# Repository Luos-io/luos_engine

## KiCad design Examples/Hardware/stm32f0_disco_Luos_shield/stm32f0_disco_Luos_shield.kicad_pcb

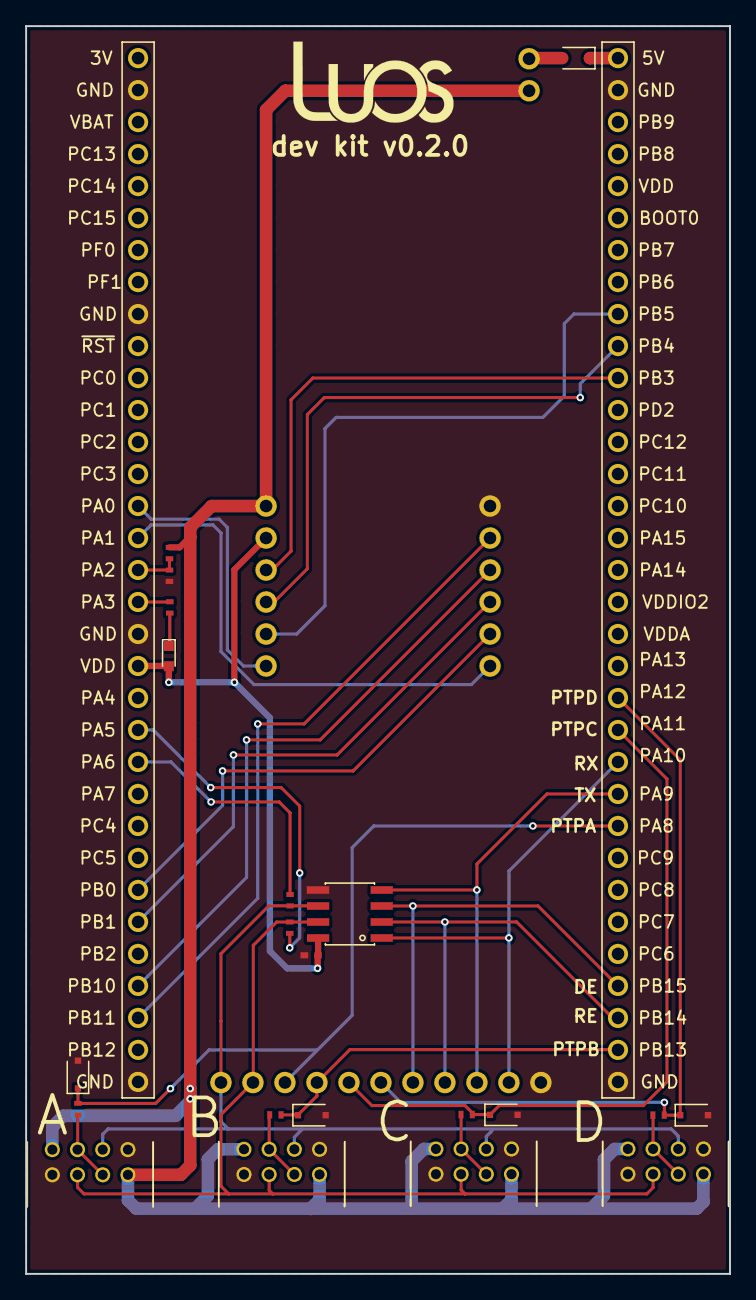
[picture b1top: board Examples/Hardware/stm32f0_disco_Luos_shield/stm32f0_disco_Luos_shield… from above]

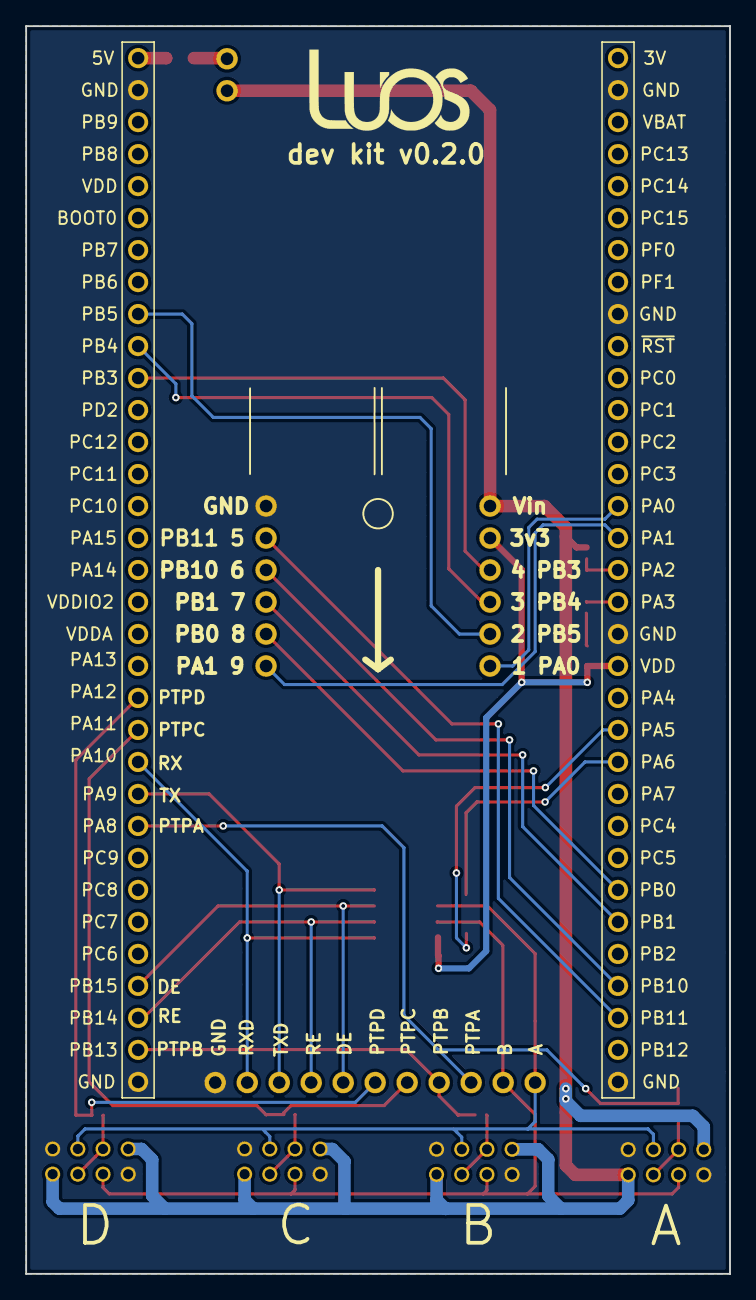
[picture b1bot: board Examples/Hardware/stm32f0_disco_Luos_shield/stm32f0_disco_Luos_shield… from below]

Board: 2 copper layers, 55.9 x 99.1 mm, 26 parts (5 on the bottom side), 33 nets.

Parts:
C1: 100nF; C_0402_NoSilk
D1, D2, D3, D4: D_Zener; D_SOD-323F
D5: DIODE; D_SOD-323F
D6: SMLE13BC8TT86; LED_0603
J1, J4: DF11-8DP-2DS; DF11-8DP-2DS(24)
J2, J3: DF11-8DP-2DS(24)
J5, J6: Header6Contacts; 826926-6
J7: Discovery_Socket
J8: Header11Contacts; 826926-11
J9: Header2Contacts; 826926-2
R1, R2, R3, R4: 100; R_0402_NoSilk
R5, R6, R8: 10K; R_0402_NoSilk
R7: 68K; R_0402_NoSilk
R9: 82; R_0402_NoSilk
U1: ST3485ECDR; SO8

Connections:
+3V3: C1.1, D6.2, J5.5, J7.5, J7.47, J7.64, J7.66, U1.8
+5VP: D5.1, J7.1
/A_RS_485_N: J1.5, J2.5, J3.5, J4.5, J8.11, R6.1, U1.6
/B_RS_485_P: J1.4, J2.4, J3.4, J4.4, J8.10, R5.2, U1.7
/DE: J7.30, J8.5, U1.3
/MISO/MCK: J5.3, J7.10
/MOSI/SD: J5.2, J7.9
/PTPA: D1.1, J7.25, J8.9, R1.1
/PTPA_PRO: J1.3, J1.6, R1.2
/PTPB: D2.1, J7.32, J8.8, R2.1
/PTPB_PRO: J2.3, J2.6, R2.2
/PTPC: D3.1, J7.22, J8.7, R3.1
/PTPC_PRO: J3.3, J3.6, R3.2
/PTPD: D4.1, J7.21, J8.6, R4.1
/PTPD_PRO: J4.3, J4.6, R4.2
/RE: J7.31, J8.4, U1.2
/RS485_LVL_DOWN: J7.45, R5.1
/RS485_LVL_UP: J7.44, R6.2
/RX/SDA/TIM2.4: J6.2, J7.36
/RxD: J7.23, J8.2, U1.1
/SCK/CK: J5.4, J7.11
/TIM2.1/ADC0: J5.1, J7.52
/TIM2.2/ADC1: J6.6, J7.51
/TIM3.3: J6.5, J7.40
/TIM3.4: J6.4, J7.39
/TX/SCL/TIM2.3: J6.3, J7.37
/TxD: J7.24, J8.3, U1.4
/Vin: J1.1, J1.8, J2.1, J2.8, J3.1, J3.8, J4.1, J4.8, J5.6, J9.1, R7.2
GND: C1.2, D1.2, D2.2, D3.2, D4.2, J1.2, J1.7, J2.2, J2.7, J3.2, J3.7, J4.2, J4.7, J6.1, J7.2, J7.33, J7.34, J7.48, J7.58, J7.65, J8.1, R8.1, U1.5
unnamed: D5.2, J9.2
unnamed: D6.1, R9.1
unnamed: J7.49, R9.2
unnamed: J7.50, R7.1, R8.2

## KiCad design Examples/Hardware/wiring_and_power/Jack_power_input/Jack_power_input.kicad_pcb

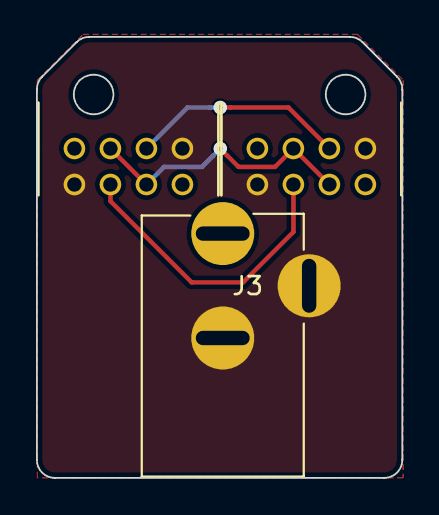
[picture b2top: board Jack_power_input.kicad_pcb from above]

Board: 2 copper layers, 20.3 x 24.5 mm, 4 parts (1 on the bottom side), 6 nets.

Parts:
D1: HTA5L45; D_SMA
J1, J2: DF11-8DP-2DS(24)
J3: DC_Power_Jack; DC_Jack_2mm

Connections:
/A_RS_485_N: J1.5, J2.5
/B_RS_485_P: J1.4, J2.4
/DC_Power: D1.2, J3.1
/PTP: J1.3, J1.6, J2.3, J2.6
/Robus_PW: D1.1, J1.1, J1.8, J2.1, J2.8
GND: J1.2, J1.7, J2.2, J2.7, J3.2, J3.3

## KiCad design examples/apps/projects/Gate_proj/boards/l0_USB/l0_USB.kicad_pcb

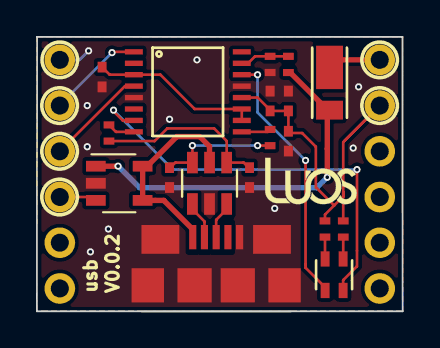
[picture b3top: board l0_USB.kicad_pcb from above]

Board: 2 copper layers, 20.3 x 15.2 mm, 19 parts (0 on the bottom side), 20 nets.

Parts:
C1, C2: 47pF; C_0402_NoSilk
C3, C4, C5: 100nF; C_0402_NoSilk
C6: 4.7uF; C_0402_NoSilk
D1: KPTB-1615ESGC
D2: DFLS230L-7; PowerDI-123
J1: µUSB_B; MicroUSB_B
J2: l0_Socket; l0_Shield_Socket
R1, R2: 27; R_0402_NoSilk
R3: 4K7; R_0402_NoSilk
R4: 10K; R_0402_NoSilk
R5: 66,5; R_0402_NoSilk
R6: 56; R_0402_NoSilk
U1: FT230X; SSOP-16
U2: STMPS2171STR; SOT-23-5
U3: USBLC6-2SC6; SOT23-6L

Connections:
+3V3: C4.1, C5.1, C6.1, J2.5, R5.1, R6.1, U1.12
+5V: J1.1, U2.4, U2.5, U3.5
/RxD: J2.9, U1.4
/Rx_LED: D1.4, U1.7
/TxD: J2.8, U1.1
/Tx_LED: D1.2, U1.14
/Vin: D2.1, J2.6
GND: C1.2, C2.2, C3.2, C4.2, C5.2, C6.2, J1.5, J2.7, R4.1, U1.5, U1.13, U2.2, U3.2
unnamed: C1.1, R2.2, U3.6
unnamed: C2.1, R1.2, U3.4
unnamed: C3.1, U1.3, U1.10, U1.11
unnamed: D1.1, R5.2
unnamed: D1.3, R6.2
unnamed: J1.2, U3.1
unnamed: J1.3, U3.3
unnamed: J2.10, U2.3
unnamed: R1.1, U1.8
unnamed: R2.1, U1.9
unnamed: R3.1, R4.2, U1.15
VBUS: D2.2, R3.2, U2.1

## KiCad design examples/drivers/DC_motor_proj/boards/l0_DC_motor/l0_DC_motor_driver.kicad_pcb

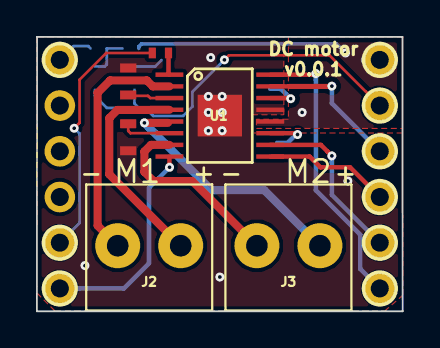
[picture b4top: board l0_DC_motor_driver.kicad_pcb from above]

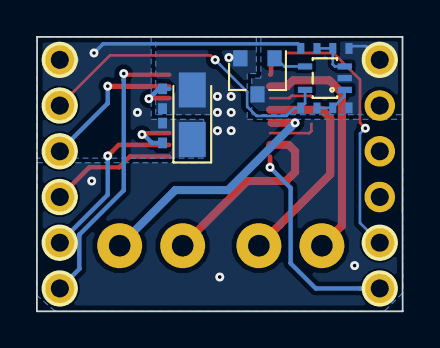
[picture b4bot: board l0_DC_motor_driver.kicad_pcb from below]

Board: 2 copper layers, 20.3 x 15.2 mm, 16 parts (9 on the bottom side), 22 nets.

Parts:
C1: 10µF; CP_Tantalum_Case-S_EIA-3216-12_Reflow
C2: 10nF; C_0402_NoSilk
C3: 2,2µF; C_0402_NoSilk
J1: l0_Socket; l0_Shield_Socket
J2, J3: 1776275-2
Q1: PMV25ENEA; SOT-23
R1: 20k; R_0402_NoSilk
R2, R3: 300m; R_0603
R4: 11.8K; R_0402_NoSilk
R5, R7: 10K; R_0402_NoSilk
R6: 68K; R_0402_NoSilk
U1: DRV8833; HTSSOP-16
U2: LMV301; SC-70-5

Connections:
+3V3: J1.5, R4.1, U2.5
/NC_PWM1: J1.1, U1.16
/NC_PWM2: J1.3, U1.9
/NO_PWM1: J1.4, U1.15
/NO_PWM2: J1.2, U1.10
/Robus_PS: C1.1, C2.1, J1.6, R6.1, U1.12
/Vmax: R4.2, R5.1, U2.1
/~nFAULT: J1.12, U1.8
/~nSLEEP: J1.11, R1.2
GND: J1.7, Q1.3, R5.2, R7.2, U2.2
GNDPWR: C1.2, C3.2, Q1.2, R2.2, R3.2, U1.13
unnamed: C2.2, U1.11
unnamed: C3.1, U1.14
unnamed: J2.1, U1.2
unnamed: J2.2, U1.4
unnamed: J3.1, U1.7
unnamed: J3.2, U1.5
unnamed: Q1.1, U2.4
unnamed: R1.1, U1.1
unnamed: R2.1, U1.6
unnamed: R3.1, U1.3
unnamed: R6.2, R7.1, U2.3

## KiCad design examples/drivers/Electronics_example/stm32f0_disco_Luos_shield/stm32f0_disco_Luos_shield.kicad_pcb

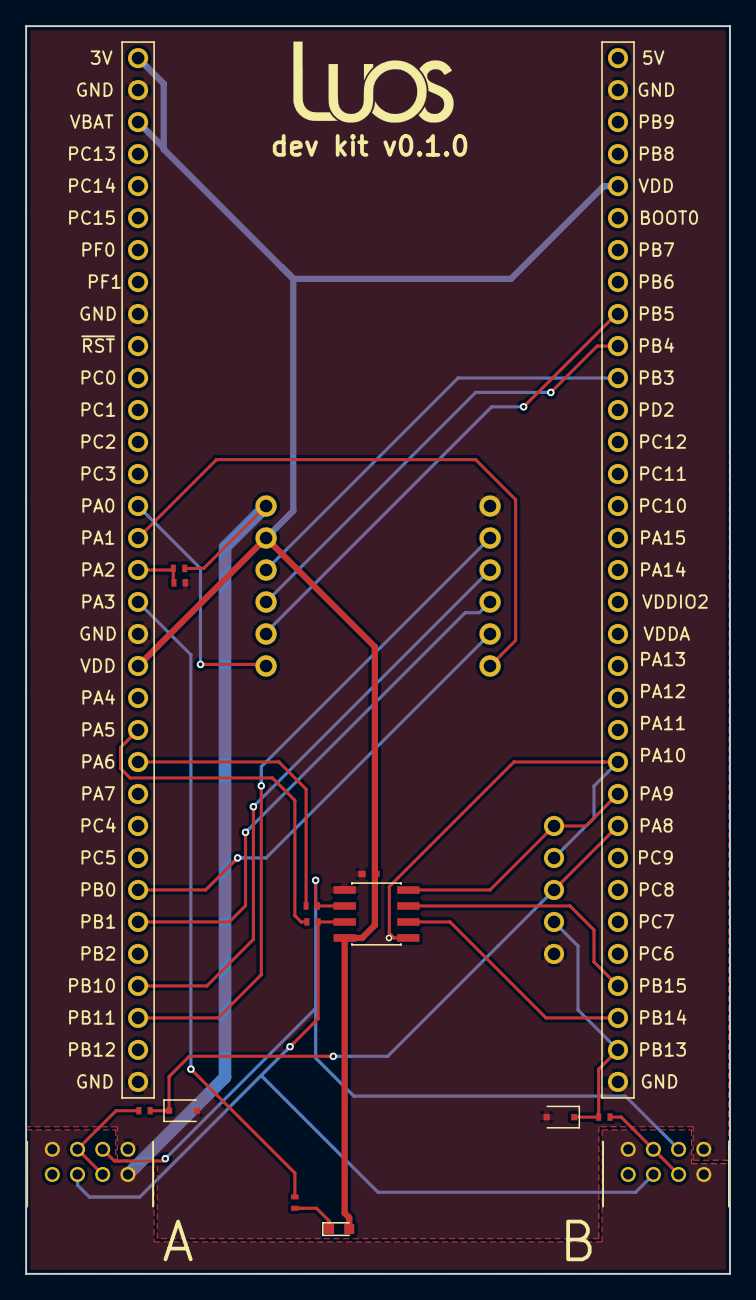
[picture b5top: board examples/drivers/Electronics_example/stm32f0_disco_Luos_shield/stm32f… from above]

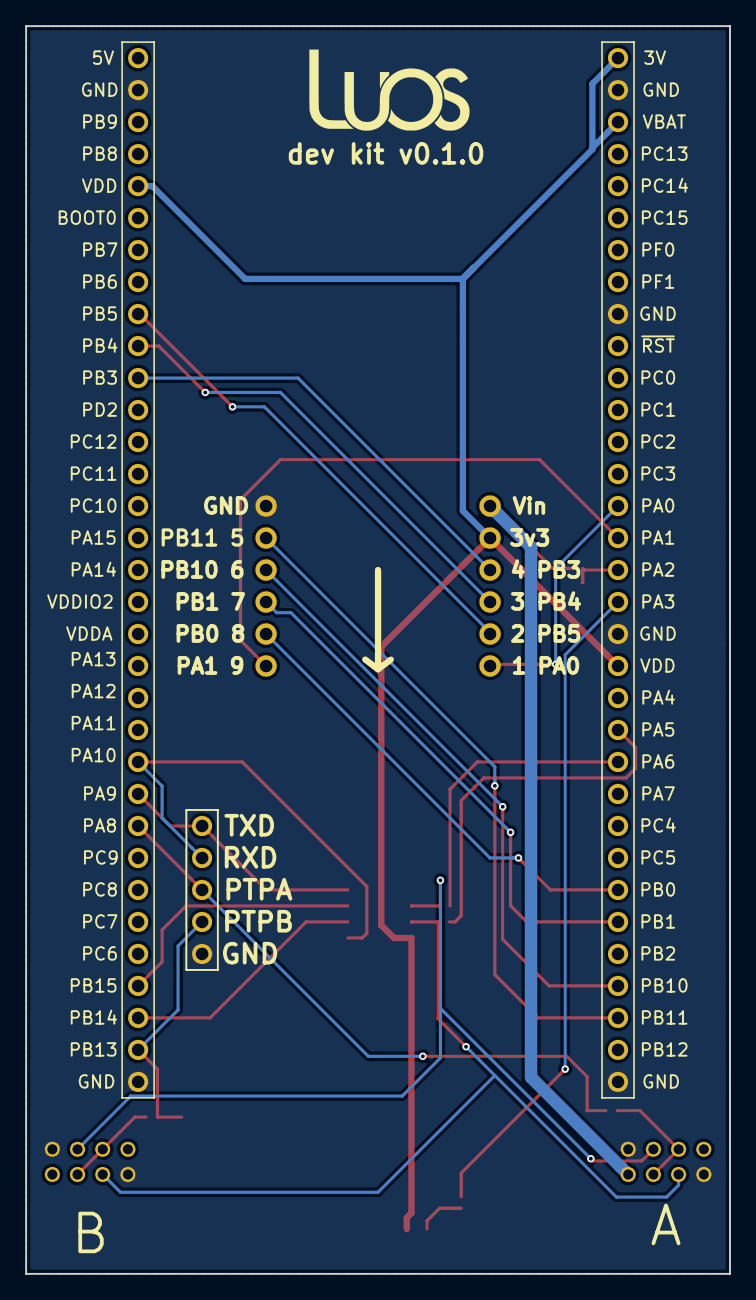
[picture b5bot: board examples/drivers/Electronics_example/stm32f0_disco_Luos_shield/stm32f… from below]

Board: 2 copper layers, 55.9 x 99.1 mm, 18 parts (4 on the bottom side), 27 nets.

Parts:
C7: 100nF; C_0402_NoSilk
D2, D3: D_Zener; D_SOD-323F
D5: SMLE13BC8TT86; LED_0603
J1, J2: DF11-8DP-2DS(24)
J3, J4: Header6Contacts; 826926-6
J5: Discovery_Socket
J6: Header5Contacts; 826926-5
R1, R2: 100; R_0402_NoSilk
R6, R7, R12: 10K; R_0402_NoSilk
R11: 68K; R_0402_NoSilk
R13: 82; R_0402_NoSilk
U1: ST3485ECDR; SO8

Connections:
+3V3: C7.1, D5.2, J3.5, J5.5, J5.47, J5.64, J5.66, U1.8
/A_RS_485_N: J1.5, J2.5, R7.1, U1.6
/B_RS_485_P: J1.4, J2.4, R6.2, U1.7
/DE: J5.30, U1.3
/MISO/MCK: J3.3, J5.10
/MOSI/SD: J3.2, J5.9
/PTPA: D3.1, J5.25, J6.3, R2.1
/PTPA_PRO: J2.3, J2.6, R2.2
/PTPB: D2.1, J5.32, J6.2, R1.1
/PTPB_PRO: J1.3, J1.6, R1.2
/RE: J5.31, U1.2
/RS485_LVL_DOWN: J5.45, R6.1
/RS485_LVL_UP: J5.44, R7.2
/RX/SDA/TIM2.4: J4.2, J5.36
/RxD: J5.23, J6.4, U1.1
/SCK/CK: J3.4, J5.11
/TIM2.1/ADC0: J3.1, J5.52
/TIM2.2/ADC1: J4.6, J5.51
/TIM3.3: J4.5, J5.40
/TIM3.4: J4.4, J5.39
/TX/SCL/TIM2.3: J4.3, J5.37
/TxD: J5.24, J6.5, U1.4
/Vin: J1.1, J1.8, J2.1, J2.8, J3.6, R11.2
GND: C7.2, D2.2, D3.2, J1.2, J1.7, J2.2, J2.7, J4.1, J5.2, J5.33, J5.34, J5.48, J5.58, J5.65, J6.1, R12.1, U1.5
unnamed: D5.1, R13.1
unnamed: J5.49, R13.2
unnamed: J5.50, R11.1, R12.2
